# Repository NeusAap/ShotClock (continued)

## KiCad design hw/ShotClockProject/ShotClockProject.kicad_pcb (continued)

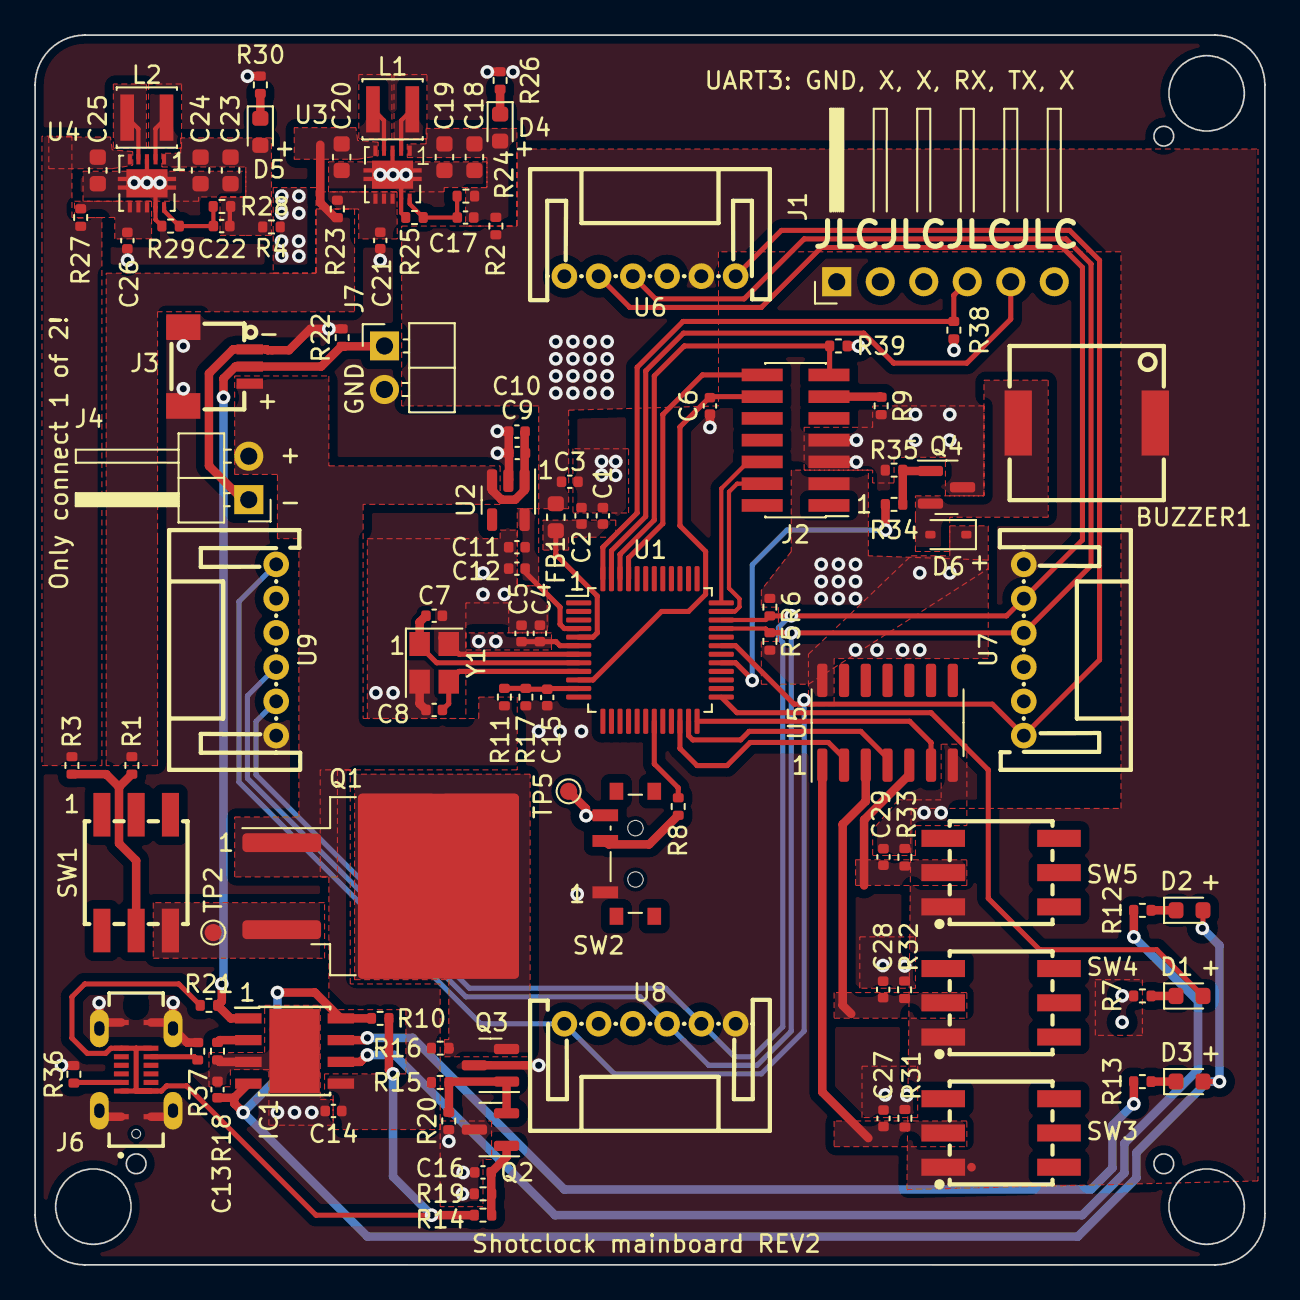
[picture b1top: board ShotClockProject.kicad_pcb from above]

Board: 4 copper layers, 71.8 x 71.8 mm, 107 parts (0 on the bottom side), 63 nets.

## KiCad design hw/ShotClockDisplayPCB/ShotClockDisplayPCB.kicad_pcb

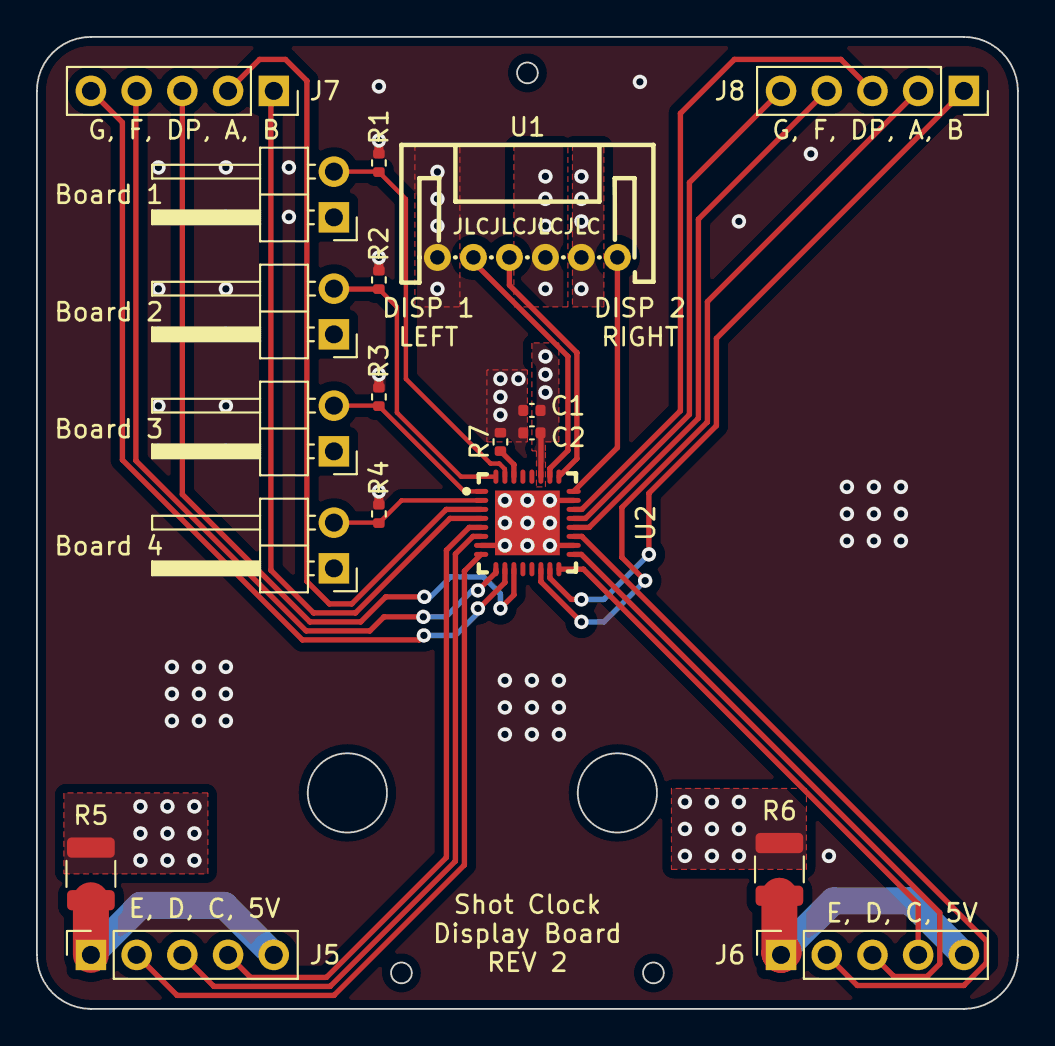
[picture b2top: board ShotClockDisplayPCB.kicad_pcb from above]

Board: 4 copper layers, 54.5 x 54.0 mm, 19 parts (0 on the bottom side), 29 nets.

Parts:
C1: 100p; C_0402_1005Metric
C2: 10u; C_0402_1005Metric
J1, J2, J3, J4: Conn_01x02_Pin; PinHeader_1x02_P2.54mm_Horizontal
J5, J6, J7, J8: Conn_01x05_Socket; PinSocket_1x05_P2.54mm_Vertical
R1, R2, R3, R4: 10k; R_0402_1005Metric
R5, R6: 100r; R_1210_3225Metric
R7: 1k; R_0402_1005Metric
U1: S6B-PH-K-S-(LF)(SN); CONN-TH_6P-P2.00_S6B-PH-K-S-LF-SN
U2: TLC59116IRHBR; PG-VQFN-32_L5.0-W5.0-P0.50-BL-EP3.6

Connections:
+3.3V: C1.1, C2.1, J1.1, J2.1, J3.1, J4.1, U1.2, U2.27 (VCC)
+5V: R5.1, R6.1, U1.3
/I2C PWM IO Expander/A0: J1.2, R1.1, U2.31 (A0)
/I2C PWM IO Expander/A1: J2.2, R2.1, U2.32 (A1)
/I2C PWM IO Expander/A2: J3.2, R3.1, U2.1 (A2)
/I2C PWM IO Expander/A3: J4.2, R4.1, U2.2 (A3)
/I2C PWM IO Expander/I2C1_SCL: U1.4, U2.25 (SCL)
/I2C PWM IO Expander/I2C1_SDA: U1.5, U2.26 (SDA)
/I2C PWM IO Expander/REXT: R7.1, U2.30 (REXT)
/I2C PWM IO Expander/TLC59116_RESETn: U1.1, U2.24 (RESET)
/Segment Display Connectors/5V_CONN1: J5.1, J5.5, R5.2
/Segment Display Connectors/5V_CONN2: J6.1, J6.5, R6.2
GND: C1.2, C2.2, R1.2, R2.2, R3.2, R4.2, R7.2, U1.6, U2.7 (GND), U2.18 (GND), U2.23 (GND), U2.33 (ep)
SEG1_A: J7.2, U2.3 (~OUT0)
SEG1_B: J7.1, U2.4 (~OUT1)
SEG1_C: J5.4, U2.5 (~OUT2)
SEG1_D: J5.3, U2.6 (~OUT3)
SEG1_DP: J7.3, U2.11 (~OUT7)
SEG1_E: J5.2, U2.8 (~OUT4)
SEG1_F: J7.4, U2.9 (~OUT5)
SEG1_G: J7.5, U2.10 (~OUT6)
SEG2_A: J8.2, U2.14 (~OUT8)
SEG2_B: J8.1, U2.15 (~OUT9)
SEG2_C: J6.4, U2.16 (~OUT10)
SEG2_D: J6.3, U2.17 (~OUT11)
SEG2_DP: J8.3, U2.22 (~OUT15)
SEG2_E: J6.2, U2.19 (~OUT12)
SEG2_F: J8.4, U2.20 (~OUT13)
SEG2_G: J8.5, U2.21 (~OUT14)

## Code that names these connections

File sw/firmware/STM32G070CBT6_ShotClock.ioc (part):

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Mcu.Name=STM32G070CBTx
Mcu.Package=LQFP48
Mcu.UserName=STM32G070CBTx
PA0.GPIOParameters=GPIO_Label
PA0.GPIO_Label=ADC_BATT_IN
PA0.Mode=IN0
PA0.Signal=ADC1_IN0
PA11\ [PA9].GPIOParameters=GPIO_Speed,GPIO_Pu,GPIO_Mode
PA11\ [PA9].GPIO_Mode=GPIO_MODE_AF_OD
PA11\ [PA9].GPIO_Pu=GPIO_NOPULL
PA11\ [PA9].GPIO_Speed=GPIO_SPEED_FREQ_LOW
PA11\ [PA9].Mode=I2C
PA11\ [PA9].Signal=I2C2_SCL
PA12\ [PA10].GPIOParameters=GPIO_Speed,GPIO_Pu,GPIO_Mode
PA12\ [PA10].GPIO_Mode=GPIO_MODE_AF_OD
PA12\ [PA10].GPIO_Pu=GPIO_NOPULL
PA12\ [PA10].GPIO_Speed=GPIO_SPEED_FREQ_LOW
PA12\ [PA10].Mode=I2C
PA12\ [PA10].Signal=I2C2_SDA
PA13.Mode=Serial_Wire
PA13.Signal=SYS_SWDIO
PA14-BOOT0.Mode=Serial_Wire
PA14-BOOT0.Signal=SYS_SWCLK
PA9.Signal=S_TIM1_CH2
PB0.GPIOParameters=GPIO_Label
PB0.GPIO_Label=BOOT0_IN
PB0.Signal=GPIO_Input
PB10.GPIOParameters=GPIO_Label,GPIO_ModeDefaultEXTI
PB10.GPIO_Label=BUTTON1_INT
PB10.GPIO_ModeDefaultEXTI=GPIO_MODE_IT_FALLING
PB10.Signal=GPXTI10
PB11.GPIOParameters=GPIO_Label,GPIO_ModeDefaultEXTI
PB11.GPIO_Label=BUTTON2_INT
PB11.GPIO_ModeDefaultEXTI=GPIO_MODE_IT_FALLING
PB11.Signal=GPXTI11
PB12.GPIOParameters=GPIO_Label,GPIO_ModeDefaultEXTI
PB12.GPIO_Label=BUTTON3_INT
PB12.GPIO_ModeDefaultEXTI=GPIO_MODE_IT_FALLING
PB12.Signal=GPXTI12
PB13.GPIOParameters=GPIO_PuPd,GPIO_Label,GPIO_ModeDefaultOutputPP
PB13.GPIO_Label=ORANGE_LED
PB13.GPIO_ModeDefaultOutputPP=GPIO_MODE_OUTPUT_PP
PB13.GPIO_PuPd=GPIO_NOPULL
PB13.Signal=GPIO_Output
PB6.Mode=Asynchronous
PB6.Signal=USART1_TX
PB7.Mode=Asynchronous
PB7.Signal=USART1_RX
PB8.Mode=Asynchronous
PB8.Signal=USART3_TX
PB9.Mode=Asynchronous
PB9.Signal=USART3_RX
PC13.GPIOParameters=GPIO_Label
PC13.GPIO_Label=BOOT0_IN
PC13.Signal=GPIO_Input
PC7.GPIOParameters=PinState,GPIO_Label
PC7.GPIO_Label=TLC59116_RESETn
PC7.PinState=GPIO_PIN_SET
PC7.Signal=GPIO_Output
PF0-OSC_IN\ (PF0).Mode=HSE-External-Oscillator
PF0-OSC_IN\ (PF0).Signal=RCC_OSC_IN
PF1-OSC_OUT\ (PF1).Mode=HSE-External-Oscillator
PF1-OSC_OUT\ (PF1).Signal=RCC_OSC_OUT
RCC.HSE_VALUE=16000000
RCC.SYSCLKFreq_VALUE=32000000
RCC.SYSCLKSource=RCC_SYSCLKSOURCE_PLLCLK
board=custom

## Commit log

2023-07-09 Init HW files
2023-07-09 HW change for testing
2023-07-09 Add .ioc file for pinouts
2023-07-09 Update readme to reflect new name
2023-07-09 Put ioc file into a firmware folder and added Py test script
2023-07-09 Changes to doc, added Py Script values and output text file
2023-07-09 Changed documentation, added to schematics
    Added Vbat connection via LDO
    Added jumper to enable/disable the TEMP pin of chrg IC.
    Added PDF exports of schematics
2023-07-09 Added PDF export of design document
2023-07-10 Added KiCAD backup files to .gitignore
    And removed existing .zip backup files.
2023-07-10 Fixed all ERC issues
    Mainly by placing PWR_FLAGs and NetTies to show KiCAD where the GNDs are connected to each other physically, without them being the same net.
2023-07-12 Init of SW, changes on HW
    SW init STMIDE project
    HW Added first few footprints for passive components.
    Removed old name .IOC file
2023-07-12 Finished footprint selection & updated design doc
    Chosen all footprints
    Updated design doc with part link & part selection reasons
2023-07-12 HW changes
    Changed Switches to correct SPDT instead of SPST.
    Added design requirements to PCB according to JLCPCB specs
2023-07-12 Updated DOCs
2023-07-12 Renamed references
2023-07-12 Init PCB
    and start on broad layout phase
2023-07-13 Changed footprint
    To horizontal 2.54 connectors
    and started on rough layout
2023-07-13 Added manufacturer folders
2023-07-13 ADded female and male headers for display PCB
2023-07-14 Added 2x10 header option
2023-07-15 Changes headers, usb schematic and footprint
    Now using standing USBc
    Header & header pins are imported
    All have 3d models now.
    Removed fp-info-cache and added it to gitignore
2023-07-15 Changed locations
2023-07-16 Finished rough layout of PCB (ready for review)
    Changed battery polarity to match the batteries I have.
    Added power led to voltage regulator
    Removed old comments from schematic
    Gave all footprints a 3D model
    Replaced batttery footprint with a SMD JST 3 pins horizontal connector
    Finished rough placement of components
2023-07-16 Added screenshot of 3D view from PCB
2023-07-18 Added encasing prototype pictures to design doc
2023-07-18 Removed old PDF exports
2023-07-18 Updated readme to explain folders
2023-07-18 Added to-do list to readme
2023-07-31 Added MSWord docx export
2023-08-10 First feedback round from Luc on schematic
2023-08-14 Changed pinouts
    To only use 1 pwm per display, and GPIo outs for the rest in both HW and firmware
2023-08-16 Started on second PCB, and added 5V regulator
    5V regulator added to main pcb for the segment displays, using same TPS63000 chip, but with a different selector resistor to choose for 5V
    Added second project to contain the display PCBA design.
    Calculated the current usage of the displays with different current limiting resistors on the LEDs.
    Calculated the current limit resistors for transistors behind LEDs
2023-08-16 Finshed both schematics
    - LED driving transistors are placed
    - All connectors on segment display PCB are placed
    - All schematic references have been re-configured (autosort on Y axis)
2023-08-16 Added footprint for MOSFET and updated PCB
2023-08-23 Updated Layout
    Placed 5V regulator
    Placed new shutoff circuit when charging
2023-08-23 Moved components around
2023-08-30 Added outline to main print
    71.8x71.8mm
2023-09-03 Add FPC conenctors
2023-09-10 Redid layout with new board dimensions
    Changed tactile switches to larger push switches (also momentary)
    Changed USART1 to UART4 & added UART5 to STDC14 connector
    Placed all components nearer to each other, and within the PCB outer edge
    Added rounded corners
2023-09-10 Moved components further from edge
    Also changed hole size, hole placement further from edge and other small dimensional changes
2023-09-10 Started on routing
    Started with decoup caps, sensitive signals and simple GPIO
2023-09-12 Routed almost everything, except display connector
2023-09-13 Added USB ESD protection
    Removed testpoints for USB+ and USB-
    Removed routes to display connectors, for another try
2023-09-13 Fixed buzzer footprint
    Almost done routing, 14 conn left.
2023-09-13 Finished routing
    Added assembly holes
    Added JLCJLCJLCJLC tag to hide their order number
2023-09-13 Added LCSC Part number
    Renamed output folders
    Created first output files for REV1
2023-09-13 Added outloiuns to the display print
2023-09-14 Display print
    Changed mainboard connector to FPC connector
    Created routing for board
2023-09-19 Added LCSC part numbers, and changed TPS vias
    - Changed the footprint for the TPS regulators, so they don't have 0.2mm vias. Manually placed GND vias next to the footprint.
    - Removed NETTIES to get rid of weird across the map connection of GND and GNDPWR.
2023-09-19 Added silkscreen and mounting holes
    Plus JLC assembly holes
2023-09-20 Start on REV2
    Decided to use 16 bit PWM IO expanders for segment displays
    Chose another STM, because F1 is out of stock (STM32G070CBT6 now)
    Replaced STM32Cube configuration with new config for G0 series.
    Updated docs to reflect new parts.
2023-09-20 Started on integrating new STM32 MCU
2023-09-23 Added I2C support
    Calculated pull-up resistor values
    Added 6 pin female headers to mainboard
    Added nRESET line for the I2C chips
    Removed PCB routing and part placement
2023-09-23 Cleaned second print
    and added new connectors, pinout and removed all REV1 stuff.
2023-09-23 Remove Lock file
2023-09-25 Changed display connectors to JST PH 2.0mm
    In docs, schematic and footprints
    Both sides, connect with male/male cable
2023-09-25 XTAL, decoup placement & I2C routing
2023-09-27 Routed V regulators on mainboard
2023-09-27 Routing on mainboard for LiPo charger
2023-10-02 Finished mainboard routing
    Reconfigered pins to make routing easier/cleaner
    Placed copper fills as much as possible to create an even plating index
2023-10-03 Finished routing and added silk + part nmbr
2023-10-03 Started on display board rework
    added new footprints
    added HW select shunts/jumpers
2023-10-04 Redid routing on disp PCB
    Added TLC chip
    Routed everything
    Used way more filled areas
2023-10-04 Realigned fill areas
2023-10-04 Changed LCSC Part numbers for disp board
2023-10-05 Fixed mainboard with feedback from Luc
2023-10-05 Rerouted display board
    And added GND planes everywhere, created step file
2023-10-06 Moved I2C traces and PWM trace
2023-10-06 Updated part NBRS for mainboard
2023-10-06 REV2 Finished
    Corrected LCSC part number
    Added polarities on silkscreen
    Made output files for both boards
2023-10-07 REV2 Finished
    Corrected LCSC part number
    Added polarities on silkscreen
    Made output files for both boards
    Added forgotten drill files
2023-10-26 Added sim project HW and start on SW
    Added CLI support on UART 1
    Added LED test cmd to enable/disable LEDs
    put the 'Debug' folder in the .gitignore
2023-10-26 Added enabling of Buzzer & button itnerrupts
2023-10-27 Set PWM to 10kz and enabled I2C_2
2023-11-03 Start on TLC driver definitions
2024-02-07 Created I2C scan func & I2C demo
2024-02-12 Add adc, addressable displays, cntdown
    ADC for voltage readout start(non correct value currently)
    All 4 sets of 2 displays are seperatly addressable now.
    Add timer function to countdown from x to 0 (currently on all 4 displays only)
2025-04-14 Add CLion support via OpenOCD
2025-08-22 Add REV3 odt file, update CubeMX version and fix the ADC readout for battery voltage.
2025-08-22 Add CLI bind for turning on/off all display segments (without the dot) at once.
2025-08-23 Added LED brightness control and test functions in CLI
